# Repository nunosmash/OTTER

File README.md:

[README.md](https://github.com/user-attachments/files/26697365/README.md)
# OTTER

**Haptic MIDI controller** that pairs analog-feel **encoder** control with DAW integration: **Live** and **Studio** modes, **haptic** feedback, **layers** and **pages**, and a **Web Editor** (Chrome) for full configuration.

Part of the **Ash Sound Works** custom tools for live and studio — by sound artist and producer **Ash (Ahn Sunghoon)** · [GitHub](https://github.com/nunosmash) / 
[Manual](http://ashsoundworks.com/otter-manual.html)

---

## Why OTTER?

Typical MIDI controllers struggle with the same tension: **analog pots** feel great, but mapping them to a DAW can cause **parameter jumps** encoders don’t always fix—especially when acceleration makes muscle-memory control unreliable on stage.

OTTER uses **encoders** with a **Live Mode** that maps rotation to a **fixed angular range** (like a pot), independent of spin speed, plus **haptic** cues at center (64) and at min/max (0 / 127). **Studio Mode** keeps fine resolution for production work. Bidirectional sync with the DAW and the Web Editor keeps names, colors, and lock logic aligned across sessions.

---

## Features

- **4 encoders** with push / rotate, **4 pages** — up to **32 parameter roles** (4×4×2 layers), plus multiple **global** and **button** mappings  
- **Live Mode** — rotation angle maps 1:1 with smoothing (stage-friendly, eyes-off control)  
- **Studio Mode** — speed-based acceleration for fast sweeps and fine edits  
- **Safety Lock** — auto-locks after page changes or idle; ~4 detents rotation to unlock  
- **Haptic motor** + **LED** feedback (center snap, boundary alerts); intensity: OFF / LOW / MID / HIGH  
- **USB MIDI** (class-compliant)  
- **Internal flash** + Web Editor sync for presets  
- **Web Editor** — latest **Chrome** ; connect via WebUSB  

---

## Specifications (summary)

| Item | Details |
|------|---------|
| Model | OTTER |
| Controls | Global / Page encoder, Encoders 1–4 (push + rotate) |
| Pages | 4 (4 encoders × 2 layers per page → up to 32 parameters) |
| I/O | USB MIDI (class-compliant) |
| Feedback | Haptic motor, LEDs |
| Storage | Internal flash, synced with Web Editor |
| Web Editor | Chrome (latest recommended) |

---

## Basic hardware behavior

- **Rotate** — increase / decrease value  
- **Short push** — layer toggle or button action (per mapping)  
- **~4 detents rotation** — unlock **Safety Lock**  
- **Global push + bottom encoder click** — device setup (DIM time, LED brightness, vibration strength, mode)  

---

## Web Editor

1. Use **Chrome** (current version).  
2. Open the bundled **OTTER Web Editor** HTML (local file or hosted URL).  
3. Connect OTTER over USB → click **Connect** in the editor and grant device access.  
4. When the status shows **Connected**, edit and sync parameters, names, and colors.  

Editor path in the site package: `otter/OTTER Web Editor.html`

---

## Firmware update (.uf2)

OTTER uses **UF2** drag-and-drop firmware (RP2040 bootloader appears as **RPI-RP2**).

1. Connect OTTER with a **data** USB cable.  
2. Hold **Button 1** and **Button 4** together for **3+ seconds** until the **RPI-RP2** drive appears.  
3. Copy the correct **`.uf2`** file onto the drive; the device reboots when done.  

---

## Repository contents

Depending on branch or release, this repo may include:

- Firmware source  
- Web Editor assets  
- Build and flash instructions  

For full mode behavior, haptics detail, and troubleshooting, see **`otter-manual.html`** in the Ash Sound Works website bundle — add your public URL once deployed.

---

| Category | Component Description | Qty |
| :--- | :--- | :---: |
| **MCU** | Raspberry Pi Pico 2 (RP2350) | 1 |
| **Display** | 2.25" TFT LCD (ST7789, 76x284 Resolution) | 1 |
| **Encoders (Primary)** | Bourns PEC11R-4015F-S0024 | 4 |
| **Encoder (Menu)** | EC11 Rotary Encoder w/ Push Switch (Detent) | 1 |
| **Haptics** | 3V 10mm Mini Vibration Coin Motor | 1 |
| **Connectors** | PJ-320A 3.5mm Stereo Jack | 1 |
| **Capacitors** | 100μF Electrolytic Capacitor | 2 |
| **Enclosure** | 121 x 43 x 2mm Clear Acrylic Top Plate | 1 |
| **Hardware** | Custom Encoder Knobs | 5 |
| **Hardware** | Brass Heat-Set Insert Nuts (M2x2x3.2) | 4 |
| **Hardware** | M2 Phillips Head Screws (M2x4) | 4 |

---

## Documentation

- Full manual: `otter-manual.html`  
- Web Editor: `otter/OTTER Web Editor.html`  
- Other projects: [github.com/nunosmash](https://github.com/nunosmash)

---

## Disclaimer

- Use a **data-capable** USB cable for editor and firmware updates.  
- DIY builds: follow safe practice for power and assembly.

---

## License

See the `LICENSE` file in the repository root.

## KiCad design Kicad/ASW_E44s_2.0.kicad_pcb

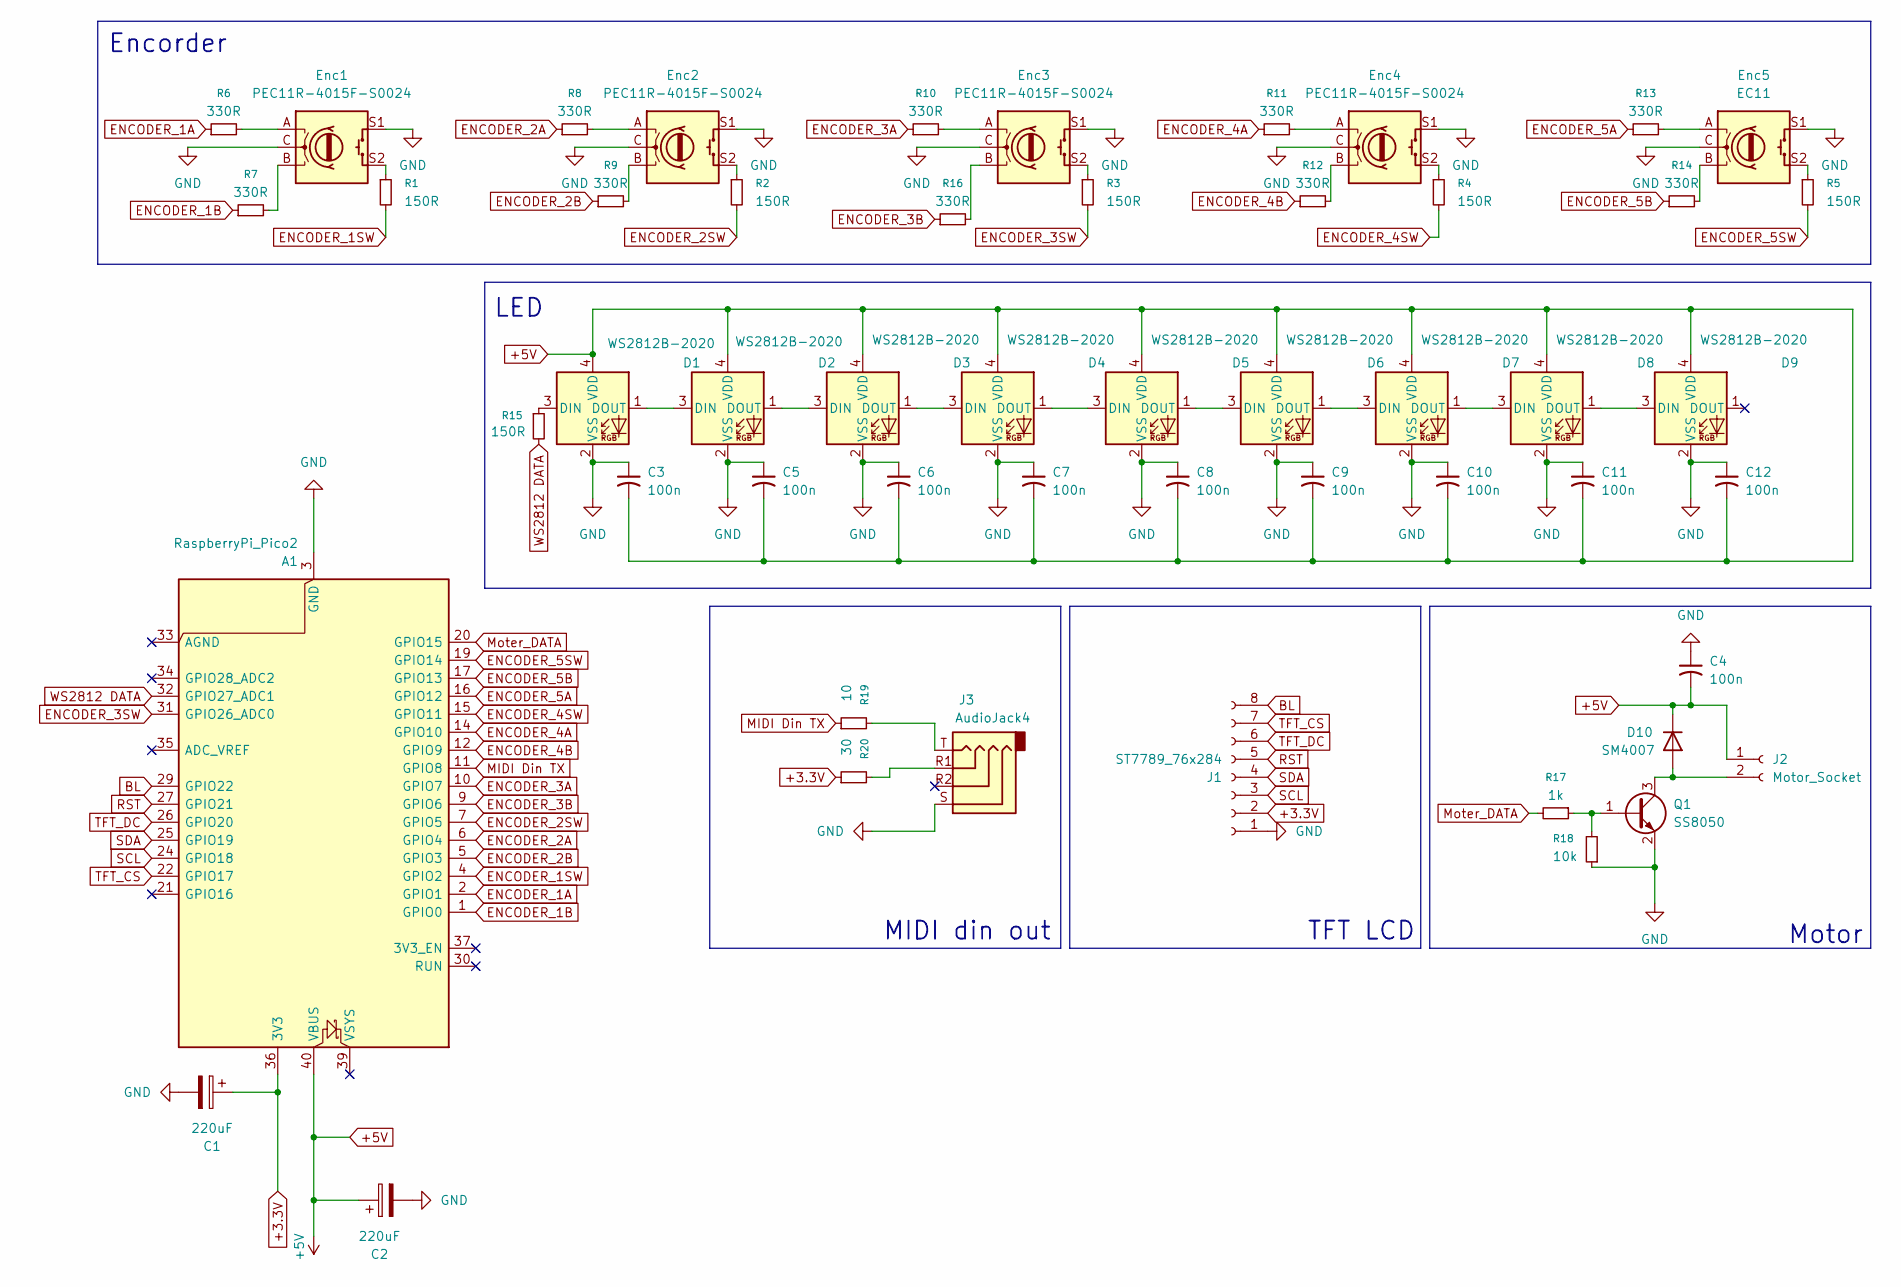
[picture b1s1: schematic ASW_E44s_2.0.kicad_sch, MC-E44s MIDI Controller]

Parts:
A1: RaspberryPi_Pico2; RaspberryPi_Pico_Common_THT2
C1, C2: 220uF; CP_Radial_D8.0mm_P3.50mm
C3, C4, C5, C6, C7, C8, C9, C10, C11, C12: 100n; C_0603_1608Metric
D1, D2, D3, D4, D5, D6, D7, D8, D9: WS2812B-2020; LED_WS2812B-2020_PLCC4_2.0x2.0mm
D10: SM4007; D_SOD-123
Enc1, Enc2, Enc3, Enc4: PEC11R-4015F-S0024; RotaryEncoder_Alps_EC11E-Switch_Vertical_H20mm
Enc5: EC11; RotaryEncoder_Alps_EC11E-Switch_Vertical_H20mm
J1: ST7789_76x284; PinHeader_1x08_P2.54mm_Vertical ST7789_76x284
J2: Motor_Socket; JST_PH_B2B-PH-K_1x02_P2.00mm_Vertical
J3: AudioJack4; PJ-320A
Q1: SS8050; SOT-23
R1, R2, R3, R4, R5, R15: 150R; R_0603_1608Metric
R6, R7, R8, R9, R10, R11, R12, R13, R14, R16: 330R; R_0603_1608Metric
R17: 1k; R_0603_1608Metric
R18: 10k; R_0603_1608Metric
R19: 10; R_0603_1608Metric
R20: 30; R_0603_1608Metric

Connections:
+3.3V: A1.36 (3V3), C1.1, J1.2, R20.1
+5V: A1.40 (VBUS), C2.1, C3.2, C4.2, C5.2, C6.2, C7.2, C8.2, C9.2, C10.2, C11.2, C12.2, D1.4 (VDD), D2.4 (VDD), D3.4 (VDD), D4.4 (VDD), D5.4 (VDD), D6.4 (VDD), D7.4 (VDD), D8.4 (VDD), D9.4 (VDD), D10.1 (K), J2.1
BL: A1.29 (GPIO22), J1.8
ENCODER_1A: A1.2 (GPIO1), R6.1
ENCODER_1B: A1.1 (GPIO0), R7.1
ENCODER_1SW: A1.4 (GPIO2), R1.2
ENCODER_2A: A1.6 (GPIO4), R8.1
ENCODER_2B: A1.5 (GPIO3), R9.1
ENCODER_2SW: A1.7 (GPIO5), R2.2
ENCODER_3A: A1.10 (GPIO7), R10.1
ENCODER_3B: A1.9 (GPIO6), R16.1
ENCODER_3SW: A1.31 (GPIO26_ADC0), R3.2
ENCODER_4A: A1.14 (GPIO10), R11.1
ENCODER_4B: A1.12 (GPIO9), R12.1
ENCODER_4SW: A1.15 (GPIO11), R4.2
ENCODER_5A: A1.16 (GPIO12), R13.1
ENCODER_5B: A1.17 (GPIO13), R14.1
ENCODER_5SW: A1.19 (GPIO14), R5.2
GND: A1.3 (GND), A1.8 (GND), A1.13 (GND), A1.18 (GND), A1.23 (GND), A1.28 (GND), A1.38 (GND), C1.2, C2.2, C3.1, C4.1, C5.1, C6.1, C7.1, C8.1, C9.1, C10.1, C11.1, C12.1, D1.2 (VSS), D2.2 (VSS), D3.2 (VSS), D4.2 (VSS), D5.2 (VSS), D6.2 (VSS), D7.2 (VSS), D8.2 (VSS), D9.2 (VSS), Enc1.C, Enc1.MP, Enc1.S1, Enc2.C, Enc2.MP, Enc2.S1, Enc3.C, Enc3.MP, Enc3.S1, Enc4.C, Enc4.MP, Enc4.S1, Enc5.C, Enc5.MP, Enc5.S1, J1.1, J3.S, Q1.2 (E), R18.1
MIDI Din TX: A1.11 (GPIO8), R19.1
Moter_DATA: A1.20 (GPIO15), R17.2
unnamed: D1.3 (DIN), R15.1
unnamed: D1.1 (DOUT), D2.3 (DIN)
unnamed: D2.1 (DOUT), D3.3 (DIN)
unnamed: D3.1 (DOUT), D4.3 (DIN)
unnamed: D4.1 (DOUT), D5.3 (DIN)
unnamed: D5.1 (DOUT), D6.3 (DIN)
unnamed: D6.1 (DOUT), D7.3 (DIN)
unnamed: D7.1 (DOUT), D8.3 (DIN)
unnamed: D8.1 (DOUT), D9.3 (DIN)
unnamed: D10.2 (A), J2.2, Q1.3 (C)
unnamed: Enc1.A, R6.2
unnamed: Enc1.B, R7.2
unnamed: Enc1.S2, R1.1
unnamed: Enc2.A, R8.2
unnamed: Enc2.B, R9.2
unnamed: Enc2.S2, R2.1
unnamed: Enc3.A, R10.2
unnamed: Enc3.B, R16.2
unnamed: Enc3.S2, R3.1
unnamed: Enc4.A, R11.2
unnamed: Enc4.B, R12.2
unnamed: Enc4.S2, R4.1
unnamed: Enc5.A, R13.2
unnamed: Enc5.B, R14.2
unnamed: Enc5.S2, R5.1
unnamed: J3.R1, R20.2
unnamed: J3.T, R19.2
unnamed: Q1.1 (B), R17.1, R18.2
RST: A1.27 (GPIO21), J1.5
SCL: A1.24 (GPIO18), J1.3
SDA: A1.25 (GPIO19), J1.4
TFT_CS: A1.22 (GPIO17), J1.7
TFT_DC: A1.26 (GPIO20), J1.6
WS2812 DATA: A1.32 (GPIO27_ADC1), R15.2

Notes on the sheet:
MIDI din out
Motor
LED
TFT LCD
Encorder

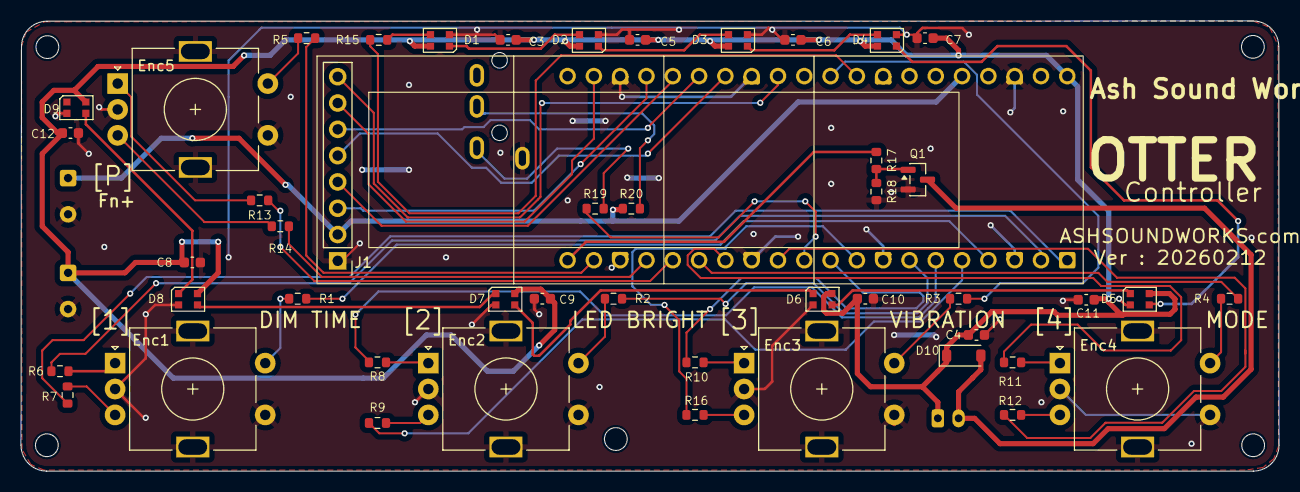
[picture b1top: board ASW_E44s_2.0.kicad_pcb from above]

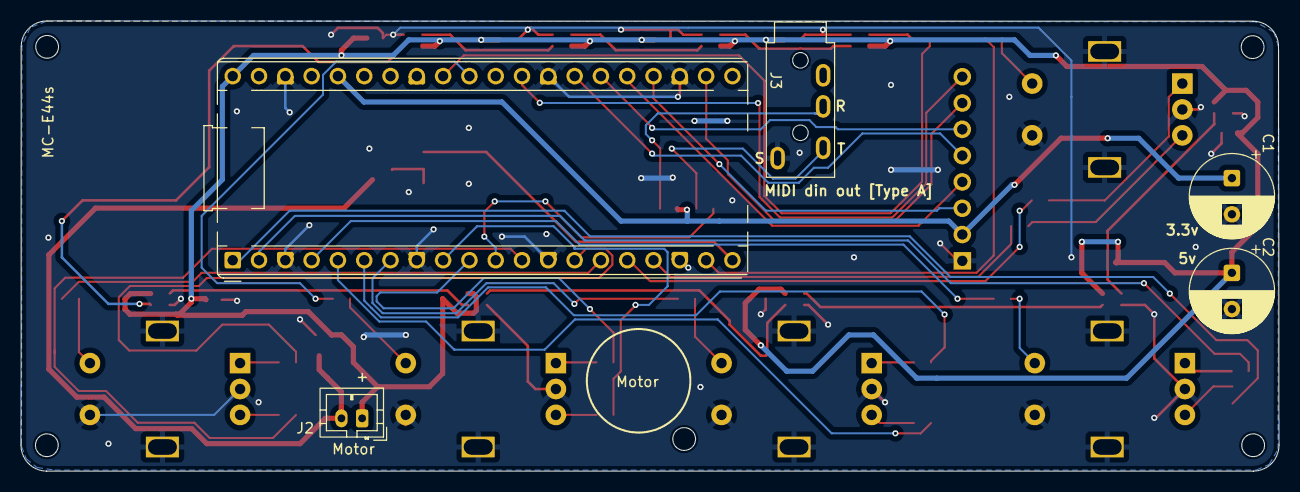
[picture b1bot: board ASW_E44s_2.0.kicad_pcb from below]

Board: 2 copper layers, 121.5 x 43.5 mm, 52 parts (5 on the bottom side), 55 nets.

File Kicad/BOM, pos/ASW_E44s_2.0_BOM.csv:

"Id";"지정자";"풋프린트";"수량";"지정";"공급자와 참조";
1;"D9,D2,D3,D5,D4,D7,D1,D6,D8";"LED_WS2812B-2020_PLCC4_2.0x2.0mm";9;"WS2812B-2020";;;
2;"";"";1;"";;;
3;"J3";"PJ-320A";1;"AudioJack4";;;
4;"J1";"PinHeader_1x08_P2.54mm_Vertical ST7789_76x284";1;"ST7789_76x284";;;
5;"R2,R15,R3,R5,R4,R1";"R_0603_1608Metric";6;"150R";;;
6;"Enc5";"RotaryEncoder_Alps_EC11E-Switch_Vertical_H20mm";1;"EC11";;;
7;"R14,R13,R10,R7,R8,R6,R16,R12,R11,R9";"R_0603_1608Metric";10;"330R";;;
8;"Enc4,Enc1,Enc3,Enc2";"RotaryEncoder_Alps_EC11E-Switch_Vertical_H20mm";4;"PEC11R-4015F-S0024";;;
9;"C10,C9,C3,C4,C8,C11,C5,C7,C12,C6";"C_0603_1608Metric";10;"100n";;;
10;"R18";"R_0603_1608Metric";1;"10k";;;
11;"R17";"R_0603_1608Metric";1;"1k";;;
12;"Q1";"SOT-23";1;"SS8050";;;
13;"D10";"D_SOD-123";1;"SM4007";;;
14;"R20";"R_0603_1608Metric";1;"30";;;
15;"R19";"R_0603_1608Metric";1;"10";;;
16;"J2";"JST_PH_B2B-PH-K_1x02_P2.00mm_Vertical";1;"Motor_Socket";;;
17;"C1,C2";"CP_Radial_D8.0mm_P3.50mm";2;"220uF";;;
18;"A1";"RaspberryPi_Pico_Common_THT2";1;"RaspberryPi_Pico2";;;

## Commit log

2026-04-28 Update README with component details
    Added a table for component descriptions and quantities.
2026-04-30 Add enclosure details to the README
2026-04-30 Clarify Web Editor compatibility in README
    Updated the README to specify that the Web Editor is compatible only with the latest version of Chrome.
